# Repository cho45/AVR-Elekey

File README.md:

消費電流
========

- パワーダウン中: 0.15uA
- キーイング中: 340uA

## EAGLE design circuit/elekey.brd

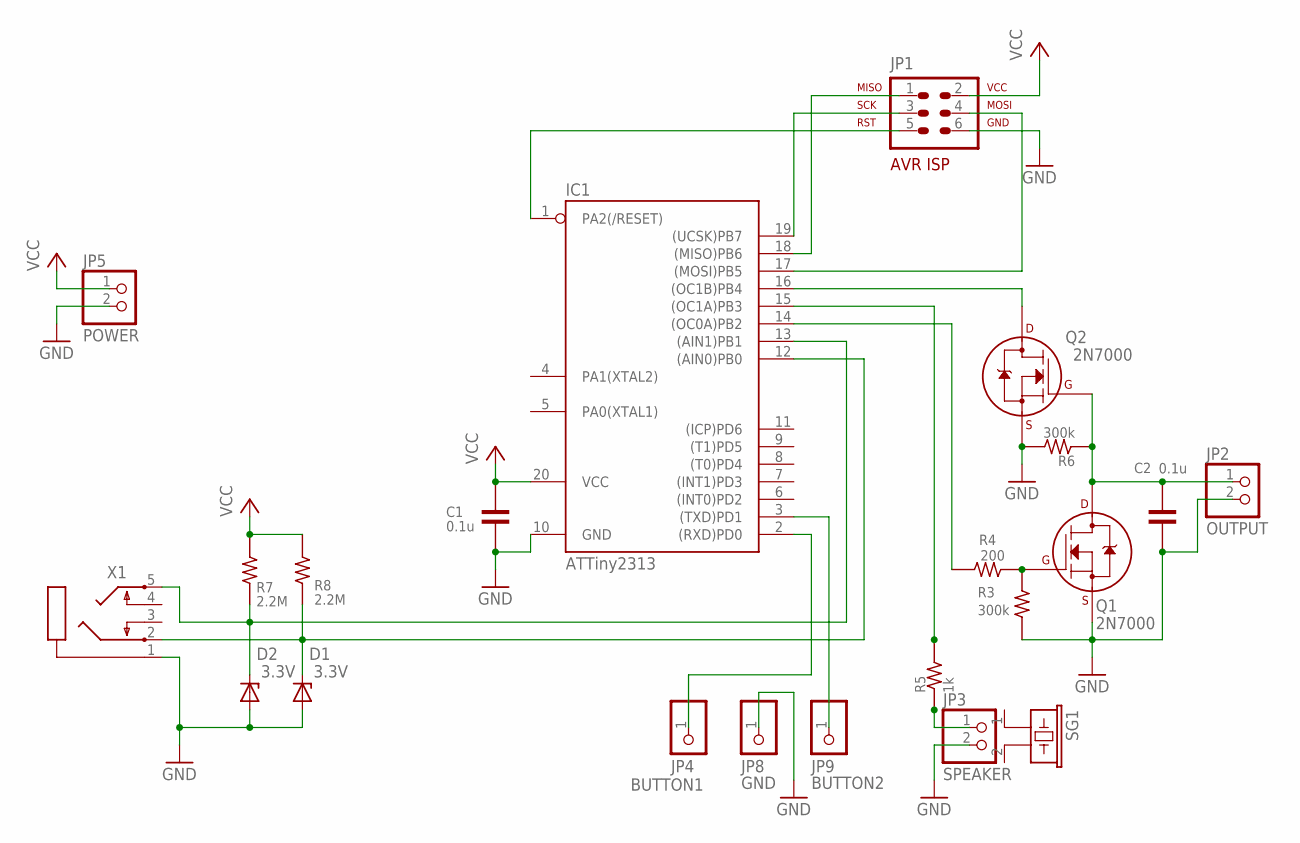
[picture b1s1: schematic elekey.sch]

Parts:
C1: 0.1u; 50-0302-2.54
C2: 0.1u; 50-0302-5.08
D1, D2: 3.3V; ZDIO-5
IC1: ATTiny2313; DIL20
JP1: AVR-ISP-6VERT; AVR-ISP-6
JP2: OUTPUT; 1X02
JP3: SPEAKER; 1X02
JP4: BUTTON1; 1X01
JP5: POWER; 1X02
JP8: GND; 1X01
JP9: BUTTON2; 1X01
Q1, Q2: 2N7000; TO-92
R3: 300k; 1/4W-2.54V
R4: 200; 1/4W-7.62H
R5: 1k; 1/4W-5.08V
R6: 300k; 1/4W-5.08V
R7: 2.2M; 1/4W-10.16H
R8: 2.2M; 1/4W-7.62H
SG1: EFBRD24C411
X1: PG203J

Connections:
GND: C1.PAD2 (2), C2.PAD2 (2), D1.A, D2.A, IC1.10 (GND), JP1.6, JP2.2, JP3.2, JP5.2, JP8.1, Q1.1 (S), Q2.1 (S), R3.PAD2 (2), R6.PAD2 (2), X1.1
unnamed: D1.C, IC1.12 ((AIN0)PB0), R8.PAD1 (1), X1.2
unnamed: D2.C, IC1.13 ((AIN1)PB1), R7.PAD1 (1), X1.5
unnamed: IC1.18 ((MISO)PB6), JP1.1
unnamed: IC1.1 (PA2(/RESET)), JP1.5
unnamed: IC1.19 ((UCSK)PB7), JP1.3
unnamed: IC1.17 ((MOSI)PB5), JP1.4
unnamed: IC1.16 ((OC1B)PB4), Q2.3 (D)
unnamed: C2.PAD1 (1), JP2.1, Q1.3 (D), Q2.2 (G), R6.PAD1 (1)
unnamed: Q1.2 (G), R3.PAD1 (1), R4.PAD1 (1)
unnamed: IC1.15 ((OC1A)PB3), R5.PAD2 (2)
unnamed: IC1.14 ((OC0A)PB2), R4.PAD2 (2)
unnamed: JP3.1, R5.PAD1 (1)
unnamed: IC1.2 ((RXD)PD0), JP4.1
unnamed: IC1.3 ((TXD)PD1), JP9.1
VCC: C1.PAD1 (1), IC1.20 (VCC), JP1.2, JP5.1, R7.PAD2 (2), R8.PAD2 (2)

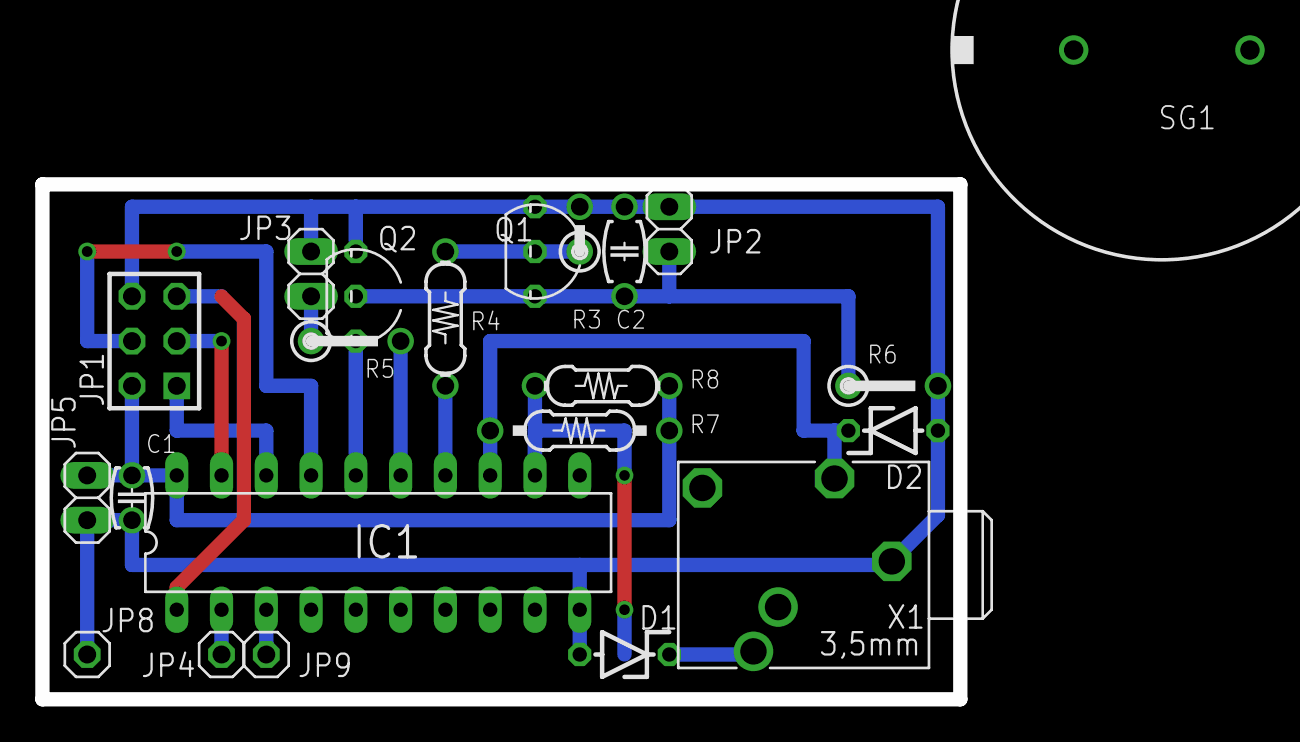
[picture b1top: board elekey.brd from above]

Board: 2 copper layers, 52.1 x 29.2 mm, 22 parts (0 on the bottom side), 16 nets.

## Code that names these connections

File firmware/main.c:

#include <avr/io.h>
#include <avr/interrupt.h>
#include <util/delay.h>
#include <avr/sleep.h>

#define INPUT_DASH PB0
#define INPUT_DOT PB1
#define OUTPUT_KEY PB2
#define SIDE_TONE_SWITCH PB4
#define SPEED_UP_KEY PD0
#define SPEED_DOWN_KEY PD1

#define SIDE_TONE_FREQ 600
#define SIDE_TONE_PIN_A OC1A
#define SIDE_TONE_PIN_B OC1B

#define INHIBIT_RATE 0.3
#define INHIBIT_TIME(speed) ((uint16_t)(1200 * INHIBIT_RATE) / speed)
#define INHIBIT_AFTER(speed) ((uint16_t)(1200 * (1 - INHIBIT_RATE)) / speed)

#define clear_bit(v, bit) v &= ~(1 << bit)
#define set_bit(v, bit)   v |=  (1 << bit)

#define CLOCK_DEVIDE 1
#define TIMER_INTERVAL (1.0 / (F_CPU / CLOCK_DEVIDE / 256) * 1000)
#define INTERVAL_UNIT_IN_MS (uint16_t)(1.0 / TIMER_INTERVAL + 0.5)
#define DURATION(msec) (uint16_t)(msec * INTERVAL_UNIT_IN_MS)

uint8_t dot_keying, dash_keying;
uint8_t speed;
uint8_t unit;

uint16_t keypressing[8];
uint8_t keydown[8], keyup[8];

uint16_t idle;
uint16_t delay;
uint16_t timer;

// Max = 65535 / INTERVAL_UNIT = 16383msec
void delay_ms(uint16_t t) {
	uint16_t end;
	cli();
	delay = 0;
	end = delay + DURATION(t);
	sei();
	while (delay <= end) {
		set_sleep_mode(SLEEP_MODE_IDLE);
		sleep_mode();
	}
}

static inline void SET_TONE(uint16_t freq) {
	if (freq) {
		TCCR1A = 0b01000001;
		OCR1A = (F_CPU / CLOCK_DEVIDE) / freq / 4;
		ICR1 = OCR1A / 2;
	} else {
		TCCR1A = 0b00000001;
	};
}

static inline void start_beep() { SET_TONE(SIDE_TONE_FREQ); }
static inline void stop_beep() { SET_TONE(0); }

static inline void start_output() {
	set_bit(PORTB, OUTPUT_KEY);
	if (bit_is_set(PINB, SIDE_TONE_SWITCH)) {
		start_beep();
	}
}

static inline void stop_output() {
	clear_bit(PORTB, OUTPUT_KEY);
	if (bit_is_set(PINB, SIDE_TONE_SWITCH)) {
		stop_beep();
	}
}

static inline void update_button_states() {
	static char prev;
	static char curr;
	static uint16_t last;
	uint8_t i;

	if (timer < last) last = timer;
	if (timer < (last + DURATION(10))) return;
	last = timer;

	curr = PIND;
	// DDRD は 7bit しかない (上位1bit不定)
	for (i = 0; i < 7; i++) {
		if (bit_is_set(DDRD, (i))) continue; // skip output port
		keydown[i] = keyup[i] = 0;

		if ( (curr ^ prev) & _BV(i)) {
			if (!keypressing[i] && bit_is_clear(curr, i)) {
				keydown[i] = 1;
			} else
			if (keypressing[i] > 0 && bit_is_set(curr, i)) {
				keyup[i] = 1;
			}
		}

		if (bit_is_clear(curr, i)) {
			keypressing[i]++;
			idle = 0;
		} else {
			keypressing[i] = 0;
		}
	}
	prev = curr;
}

static inline void clear_button_states() {
	uint8_t i;
	for (i = 0; i < 8; i++){
		keypressing[i] = 0;
		keyup[i] = 0;
		keydown[i] = 0;
	}
}


void _play(uint8_t number) {
	static uint32_t numbers[] = {
		0b1110111011101110111,
		0b10111011101110111,
		0b101011101110111,
		0b1010101110111,
		0b10101010111,
		0b101010101,
		0b11101010101,
		0b1110111010101,
		0b111011101110101,
		0b11101110111011101,
	};

	uint32_t n = numbers[number];
	uint8_t i = 0;

	for (i = 0; i < 32; i++) {
		if (n >> (31 - i) & 1) {
			i -= 1;
			break;
		}
	}

	for (; i < 32; i++) {
		if (n >> (31 - i) & 1) {
			start_beep();
			delay_ms(unit);
		} else {
			stop_beep();
			delay_ms(unit);
		}
	}
	stop_beep();
}

void play(uint8_t num) {
	_play(num / 10);
	delay_ms(unit * 2);
	_play(num % 10);
}


/**
 * メインループはビジーループに入ったりするので、割り込みでボタン状態を見る
 *
 */
ISR(TIMER0_OVF_vect) {
	delay++;
	timer++;
	idle++;

	if (bit_is_clear(PINB, INPUT_DOT)) {
		dot_keying = 1;
	}

	if (bit_is_clear(PINB, INPUT_DASH)) {
		dash_keying = 1;
	}
}

/**
 * キーの入力レベルが変わったとき (押したとき・離したとき) に割込みがかかる
 *
 */
ISR(PCINT_vect) {
	idle = 0;
}

void play_ok() {
	start_beep();
	delay_ms(unit * 3);
	stop_beep();
	delay_ms(unit);
	start_beep();
	delay_ms(unit);
	stop_beep();
	delay_ms(unit);
	start_beep();
	delay_ms(unit * 3);
	stop_beep();
	delay_ms(unit);
}

void play_beep() {
	SET_TONE(800);
	delay_ms(100);
	SET_TONE(1200);
	delay_ms(150);
	SET_TONE(0);
}

void setup_io() {
	/**
	 * Data Direction Register: 0=input, 1=output
	 * 必要なポートだけインプットポートにする。
	 */
	DDRA  = 0b11111111;
	DDRB  = 0b11101100;
	DDRD  = 0b11111100;

	/**
	 * Pull-up puddle pin
	 * 入力ピンをオープンにすると不安定になるので、プルアップ(VCCに繋げる)して
	 * 電位を安定させる。スイッチは PIN <-> SWITCH <-> GND となり、押したときに
	 * GND すなわち0になる
	 */
	PORTB = 0b00010000;
	PORTD = 0b00000011;

	/**
	 * Timer0 の分周設定
	 * TCCR0B 下位3bit
	 *  000 -> 停止
	 *  001 -> 分周なし
	 *  010 -> 8分周
	 *  011 -> 64分周
	 *  100 -> 256分周
	 *  101 -> 1024分周
	 */
	TCCR0A = 0b00000000;
	TCCR0B = 0b00000001;

	/**
	 * Timer0 のオーバーフロー割り込みを有効化
	 */
	TIMSK = 0b00000010;
	//set_bit(TIMSK, TOIE0);

	/**
	 * Timer1 の設定
	 * 位相・周波数 PWM
	 * 0 から top まで登りカウントして、途中 compare を超えると出力がHになり、
	 * 今度は 0 まで下りカウントして途中 compare を下まわると出力がLになる。
	 * 今回はただの圧電スピーカー駆動なので duty 比 50% (compare が常に 1/2) にしてる
	 * */
	// WGM13=1, WGM12=0, WGM11=0, WGM10=1
	TCCR1A = 0b01000001;
	TCCR1B = 0b00010001;

	/**
	 * キー割り込み
	 * スリープ復帰用
	 */ 
	GIMSK = 0b00100000;
	PCMSK = (1<<PCINT0)|(1<<PCINT1);

	/**
	 * 割り込み有効化
	 */
	sei();

}

int main(void) {
	uint8_t enable = 1;

	setup_io();

	speed = 20;
	unit = 1200 / speed;
	timer = 0;
	delay = 0;
	idle = 0;

	clear_button_states();

	/**
	 * ini message
	 */
	play_beep();

	for (;;) {
		update_button_states();

		if (keypressing[SPEED_UP_KEY] > 200 && keypressing[SPEED_DOWN_KEY] > 200) {
			play_ok();
			enable = !enable;
			delay_ms(500);
			clear_button_states();
		} else
		if (
			(keypressing[SPEED_UP_KEY] > 200 && !keypressing[SPEED_DOWN_KEY]) || 
			(keypressing[SPEED_DOWN_KEY] > 200 && !keypressing[SPEED_UP_KEY])
		) {
			play(speed);
			delay_ms(500);
			clear_button_states();
		}


		if (keyup[SPEED_UP_KEY]) {
			if (speed < 40) {
				speed++;
				unit = (int)(1200 / speed);
				play_beep();
				delay_ms(200);
			}
		}

		if (keyup[SPEED_DOWN_KEY]) {
			if (1 < speed) {
				speed--;
				unit = (int)(1200 / speed);
				play_beep();
				delay_ms(200);
			}
		};

		if (enable) {
			if (dot_keying) {
				start_output();
				delay_ms(unit);
				stop_output();
				delay_ms(INHIBIT_TIME(speed));
				dot_keying = 0;
				delay_ms(INHIBIT_AFTER(speed));
				idle = 0;
			}

			if (dash_keying) {
				start_output();
				delay_ms(unit * 3);
				stop_output();
				delay_ms(INHIBIT_TIME(speed));
				dash_keying = 0;
				delay_ms(INHIBIT_AFTER(speed));
				idle = 0;
			}
		} else {
			while (bit_is_clear(PINB, INPUT_DOT) || bit_is_clear(PINB, INPUT_DASH)) {
				start_output();
				_delay_ms(10);
			}
			stop_output();
			dot_keying = dash_keying = 0;
		}

		// 10000msec 経ったらパワーダウン
		if (idle > DURATION(10000)) {
			set_sleep_mode(SLEEP_MODE_PWR_DOWN);
			sleep_mode();
			timer = 0;
		} else {
			set_sleep_mode(SLEEP_MODE_IDLE);
			sleep_mode();
		}
	}
	return 0;
}

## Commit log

2013-10-11 init
2013-10-12 elekey
2013-10-12 speed control
2013-10-12 省電力化
2013-10-12 macro を減らしとく
2013-10-12 inline function よくわからなすぎるのでやめた
2013-10-13 同時押しとかを実装。。http://www.adafruit.com/blog/2009/10/20/example-code-for-multi-button-checker-with-debouncing/
2013-10-13 idle にならない
2013-10-13 1MHz クロックバージョン
2013-10-13 8MHz、パワーダウンモードからの復帰が遅すぎてつらい
2013-10-13 setup_io
2013-10-13 bug...
2013-10-14 Fix idle
2013-10-14 1MHz
2013-10-14 Update fuse
2013-10-15 符号スピードが遅すぎるのでもどす
2013-10-17 use counter for delay
2013-10-17 消費電流減らし
2013-10-17 ISP をやめれば電流流れなくなるのでやめた
2013-10-18 リグ側に電圧がかからないように FET でスイッチするように
2013-10-22 inhibit
2013-10-22 circuit
2013-10-22 inhibit 精度向上
2013-11-09 eagle
2013-11-10 コメントがおかしい
2013-11-13 tone 周波数がおかしい…
